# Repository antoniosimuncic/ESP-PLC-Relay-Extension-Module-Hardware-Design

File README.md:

# ESP-PLC-Relay-Extension-Module-Hardware-Design
ESP-PLC Relay-Extension-Module-Hardware-Design

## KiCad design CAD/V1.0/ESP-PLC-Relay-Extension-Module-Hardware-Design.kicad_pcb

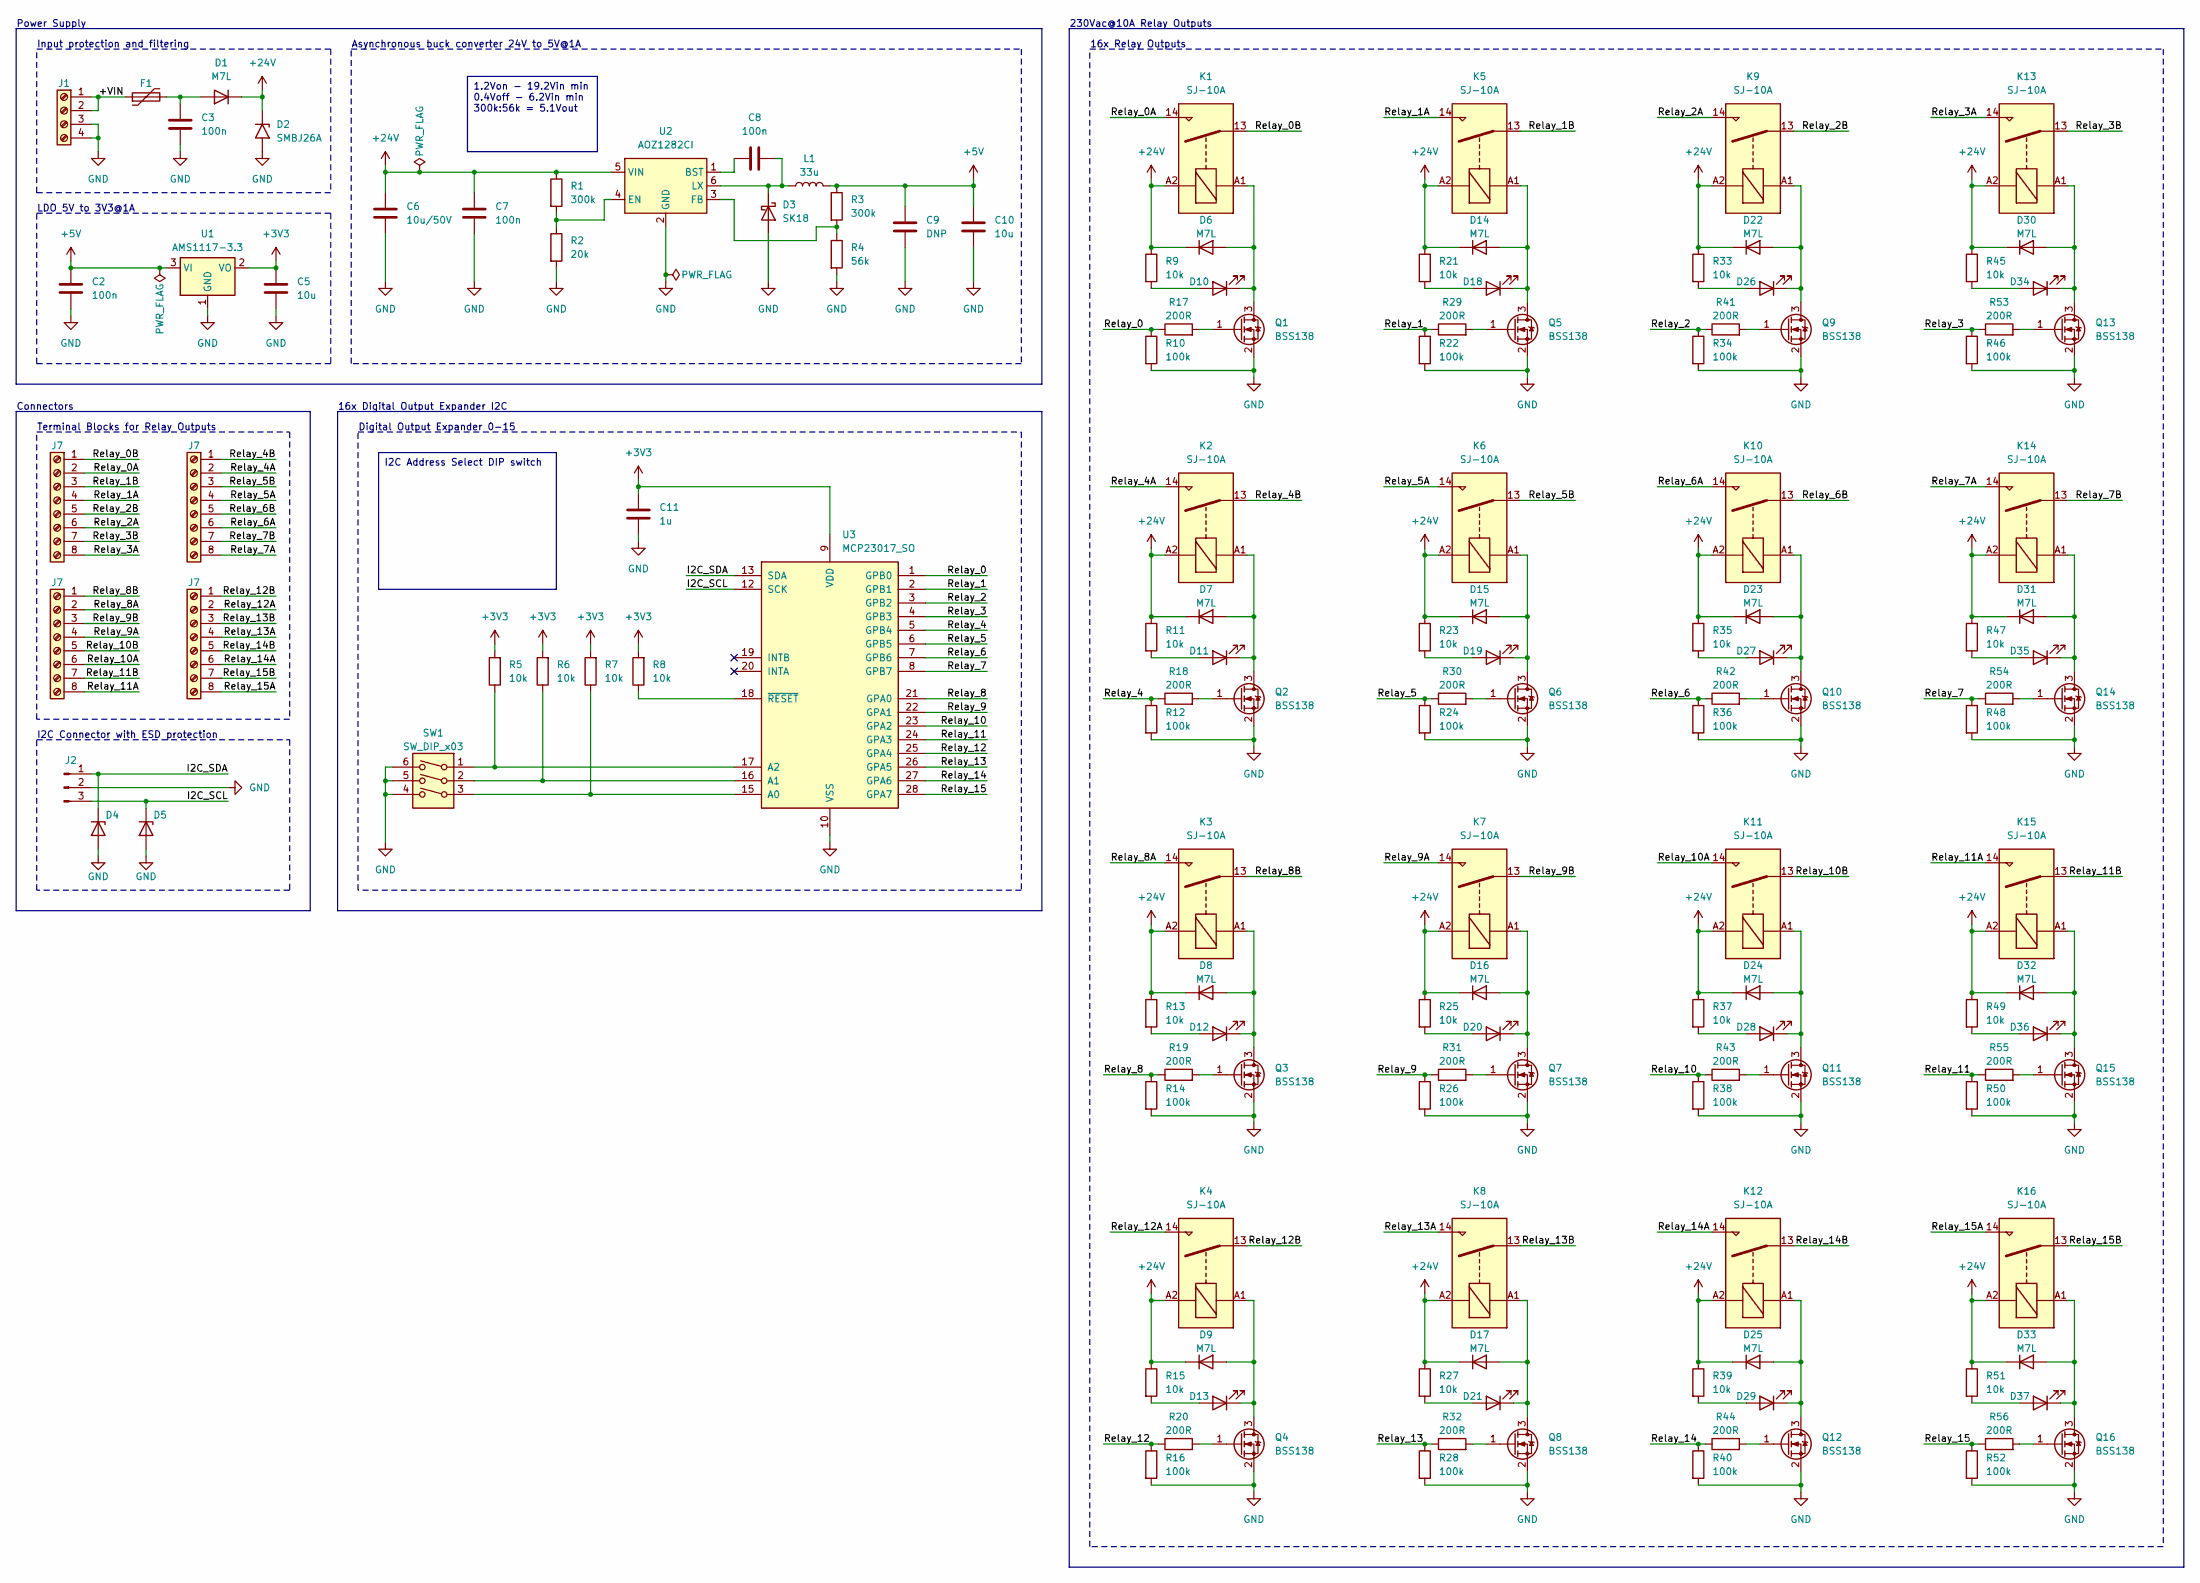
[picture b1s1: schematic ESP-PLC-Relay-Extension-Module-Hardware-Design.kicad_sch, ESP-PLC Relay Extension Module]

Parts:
C2, C3, C7, C8: 100n; C_0603_1608Metric
C5, C10: 10u; C_0805_2012Metric
C6: 10u/50V; C_1206_3216Metric
C9: DNP; C_0805_2012Metric
C11: 1u; C_0805_2012Metric
D1, D6, D7, D8, D9, D14, D15, D16, D17, D22, D23, D24, D25, D30, D31, D32, D33: M7L; D_SMA
D2: SMBJ26A; D_SMB
D3: SK18; D_SMA
D4, D5: ESD5Z3.3T1G; D_SOD-523
D10, D11, D12, D13, D18, D19, D20, D21, D26, D27, D28, D29, D34, D35, D36, D37: LED; LED_0805_2012Metric
F1: 0ZCH0010FF2E; Fuse_1210_3225Metric
J1: Screw_Terminal_01x04; PhoenixContact_MSTBVA_2,5_4-G-5,08_1x04_P5.08mm_Vertical
J2: Conn_01x03_Pin; JST_XH_B3B-XH-A_1x03_P2.50mm_Vertical
J7: Screw_Terminal_01x08; PhoenixContact_MSTBA_2,5_8-G-5,08_1x08_P5.08mm_Horizontal
K1, K2, K3, K4, K5, K6, K7, K8, K9, K10, K11, K12, K13, K14, K15, K16: SJ-10A; Relay_SJ-10A
L1: 33u; L_FerroCore_HPI1040_10.8x10.0mm
Q1, Q2, Q3, Q4, Q5, Q6, Q7, Q8, Q9, Q10, Q11, Q12, Q13, Q14, Q15, Q16: BSS138; SOT-23
R1, R3: 300k; R_0603_1608Metric
R2: 20k; R_0603_1608Metric
R4: 56k; R_0603_1608Metric
R5, R6, R7, R8, R9, R11, R13, R15, R21, R23, R25, R27, R33, R35, R37, R39, R45, R47, R49, R51: 10k; R_0603_1608Metric
R10, R12, R14, R16, R22, R24, R26, R28, R34, R36, R38, R40, R46, R48, R50, R52: 100k; R_0603_1608Metric
R17, R18, R19, R20, R29, R30, R31, R32, R41, R42, R43, R44, R53, R54, R55, R56: 200R; R_0603_1608Metric
SW1: SW_DIP_x03; SW_DIP_SPSTx03_Slide_9.78x9.8mm_W7.62mm_P2.54mm
U1: AMS1117-3.3; SOT-223-3_TabPin2
U2: AOZ1282CI; SOT-23-6
U3: MCP23017_SO; SOIC-28W_7.5x17.9mm_P1.27mm

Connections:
+3V3: C5.1, C11.1, R5.2, R6.2, R7.2, R8.2, U1.2 (VO), U3.9 (VDD)
+5V: C2.1, C9.1, C10.1, L1.2, R3.1, U1.3 (VI)
+24V: C6.1, C7.1, D1.1 (K), D2.1 (A1), D6.1 (K), D7.1 (K), D8.1 (K), D9.1 (K), D14.1 (K), D15.1 (K), D16.1 (K), D17.1 (K), D22.1 (K), D23.1 (K), D24.1 (K), D25.1 (K), D30.1 (K), D31.1 (K), D32.1 (K), D33.1 (K), K1.A2, K2.A2, K3.A2, K4.A2, K5.A2, K6.A2, K7.A2, K8.A2, K9.A2, K10.A2, K11.A2, K12.A2, K13.A2, K14.A2, K15.A2, K16.A2, R1.1, R9.1, R11.1, R13.1, R15.1, R21.1, R23.1, R25.1, R27.1, R33.1, R35.1, R37.1, R39.1, R45.1, R47.1, R49.1, R51.1, U2.5 (VIN)
/+VIN: F1.1, J1.1, J1.2
/I2C_SCL: D5.1 (K), J2.3, U3.12 (SCK)
/I2C_SDA: D4.1 (K), J2.1, U3.13 (SDA)
/Relay_0: R10.1, R17.1, U3.1 (GPB0)
/Relay_0A: K1.14; also elsewhere on the board
/Relay_0B: K1.13; also elsewhere on the board
/Relay_1: R22.1, R29.1, U3.2 (GPB1)
/Relay_1A: K5.14; also elsewhere on the board
/Relay_1B: K5.13; also elsewhere on the board
/Relay_2: R34.1, R41.1, U3.3 (GPB2)
/Relay_2A: K9.14; also elsewhere on the board
/Relay_2B: K9.13; also elsewhere on the board
/Relay_3: R46.1, R53.1, U3.4 (GPB3)
/Relay_3A: K13.14; also elsewhere on the board
/Relay_3B: K13.13; also elsewhere on the board
/Relay_4: R12.1, R18.1, U3.5 (GPB4)
/Relay_4A: K2.14; also elsewhere on the board
/Relay_4B: K2.13; also elsewhere on the board
/Relay_5: R24.1, R30.1, U3.6 (GPB5)
/Relay_5A: K6.14; also elsewhere on the board
/Relay_5B: K6.13; also elsewhere on the board
/Relay_6: R36.1, R42.1, U3.7 (GPB6)
/Relay_6A: K10.14; also elsewhere on the board
/Relay_6B: K10.13; also elsewhere on the board
/Relay_7: R48.1, R54.1, U3.8 (GPB7)
/Relay_7A: K14.14; also elsewhere on the board
/Relay_7B: K14.13; also elsewhere on the board
/Relay_8: R14.1, R19.1, U3.21 (GPA0)
/Relay_8A: K3.14; also elsewhere on the board
/Relay_8B: K3.13; also elsewhere on the board
/Relay_9: R26.1, R31.1, U3.22 (GPA1)
/Relay_9A: K7.14; also elsewhere on the board
/Relay_9B: K7.13; also elsewhere on the board
/Relay_10: R38.1, R43.1, U3.23 (GPA2)
/Relay_10A: K11.14; also elsewhere on the board
/Relay_10B: K11.13; also elsewhere on the board
/Relay_11: R50.1, R55.1, U3.24 (GPA3)
/Relay_11A: K15.14; also elsewhere on the board
/Relay_11B: K15.13; also elsewhere on the board
/Relay_12: R16.1, R20.1, U3.25 (GPA4)
/Relay_12A: K4.14; also elsewhere on the board
/Relay_12B: K4.13; also elsewhere on the board
/Relay_13: R28.1, R32.1, U3.26 (GPA5)
/Relay_13A: K8.14; also elsewhere on the board
/Relay_13B: K8.13; also elsewhere on the board
/Relay_14: R40.1, R44.1, U3.27 (GPA6)
/Relay_14A: K12.14; also elsewhere on the board
/Relay_14B: K12.13; also elsewhere on the board
/Relay_15: R52.1, R56.1, U3.28 (GPA7)
/Relay_15A: K16.14; also elsewhere on the board
/Relay_15B: K16.13; also elsewhere on the board
GND: C2.2, C3.2, C5.2, C6.2, C7.2, C9.2, C10.2, C11.2, D2.2 (A2), D3.2 (A), D4.2 (A), D5.2 (A), J1.3, J1.4, J2.2, Q1.2 (S), Q2.2 (S), Q3.2 (S), Q4.2 (S), Q5.2 (S), Q6.2 (S), Q7.2 (S), Q8.2 (S), Q9.2 (S), Q10.2 (S), Q11.2 (S), Q12.2 (S), Q13.2 (S), Q14.2 (S), Q15.2 (S), Q16.2 (S), R2.2, R4.2, R10.2, R12.2, R14.2, R16.2, R22.2, R24.2, R26.2, R28.2, R34.2, R36.2, R38.2, R40.2, R46.2, R48.2, R50.2, R52.2, SW1.4, SW1.5, SW1.6, U1.1 (GND), U2.2 (GND), U3.10 (VSS)
unnamed: C3.1, D1.2 (A), F1.2
unnamed: C8.1, D3.1 (K), L1.1, U2.6 (LX)
unnamed: D10.2 (A), R9.2
unnamed: D6.2 (A), D10.1 (K), K1.A1, Q1.3 (D)
unnamed: D11.2 (A), R11.2
unnamed: D7.2 (A), D11.1 (K), K2.A1, Q2.3 (D)
unnamed: D12.2 (A), R13.2
unnamed: D8.2 (A), D12.1 (K), K3.A1, Q3.3 (D)
unnamed: D13.2 (A), R15.2
unnamed: D9.2 (A), D13.1 (K), K4.A1, Q4.3 (D)
unnamed: D14.2 (A), D18.1 (K), K5.A1, Q5.3 (D)
unnamed: D15.2 (A), D19.1 (K), K6.A1, Q6.3 (D)
unnamed: D16.2 (A), D20.1 (K), K7.A1, Q7.3 (D)
unnamed: D17.2 (A), D21.1 (K), K8.A1, Q8.3 (D)
unnamed: D18.2 (A), R21.2
unnamed: D19.2 (A), R23.2
unnamed: D20.2 (A), R25.2
unnamed: D21.2 (A), R27.2
unnamed: D22.2 (A), D26.1 (K), K9.A1, Q9.3 (D)
unnamed: D23.2 (A), D27.1 (K), K10.A1, Q10.3 (D)
unnamed: D24.2 (A), D28.1 (K), K11.A1, Q11.3 (D)
unnamed: D25.2 (A), D29.1 (K), K12.A1, Q12.3 (D)
unnamed: D26.2 (A), R33.2
unnamed: D27.2 (A), R35.2
unnamed: D28.2 (A), R37.2
unnamed: D29.2 (A), R39.2
unnamed: D30.2 (A), D34.1 (K), K13.A1, Q13.3 (D)
unnamed: D31.2 (A), D35.1 (K), K14.A1, Q14.3 (D)
unnamed: D32.2 (A), D36.1 (K), K15.A1, Q15.3 (D)
unnamed: D33.2 (A), D37.1 (K), K16.A1, Q16.3 (D)
unnamed: D34.2 (A), R45.2
unnamed: D35.2 (A), R47.2
unnamed: D36.2 (A), R49.2
unnamed: D37.2 (A), R51.2
unnamed: Q1.1 (G), R17.2
unnamed: Q2.1 (G), R18.2
unnamed: Q3.1 (G), R19.2
unnamed: Q4.1 (G), R20.2
unnamed: Q5.1 (G), R29.2
unnamed: Q6.1 (G), R30.2
unnamed: Q7.1 (G), R31.2
unnamed: Q8.1 (G), R32.2
unnamed: Q9.1 (G), R41.2
unnamed: Q10.1 (G), R42.2
unnamed: Q11.1 (G), R43.2
unnamed: Q12.1 (G), R44.2
unnamed: Q13.1 (G), R53.2
unnamed: Q14.1 (G), R54.2
unnamed: Q15.1 (G), R55.2
unnamed: Q16.1 (G), R56.2
unnamed: C8.2, U2.1 (BST)
unnamed: R1.2, R2.1, U2.4 (EN)
unnamed: R3.2, R4.1, U2.3 (FB)
unnamed: R7.1, SW1.3, U3.15 (A0)
unnamed: R6.1, SW1.2, U3.16 (A1)
unnamed: R5.1, SW1.1, U3.17 (A2)
unnamed: R8.1, U3.18 (~RESET)

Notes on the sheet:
1.2Von - 19.2Vin min 0.4Voff - 6.2Vin min 300k:56k = 5.1Vout
I2C Address Select DIP switch
Terminal Blocks for Relay Outputs
Power Supply
16x Digital Output Expander I2C
230Vac@10A Relay Outputs
LDO 5V to 3V3@1A
Connectors
Digital Output Expander 0-15
16x Relay Outputs
Asynchronous buck converter 24V to 5V@1A
Input protection and filtering
I2C Connector with ESD protection

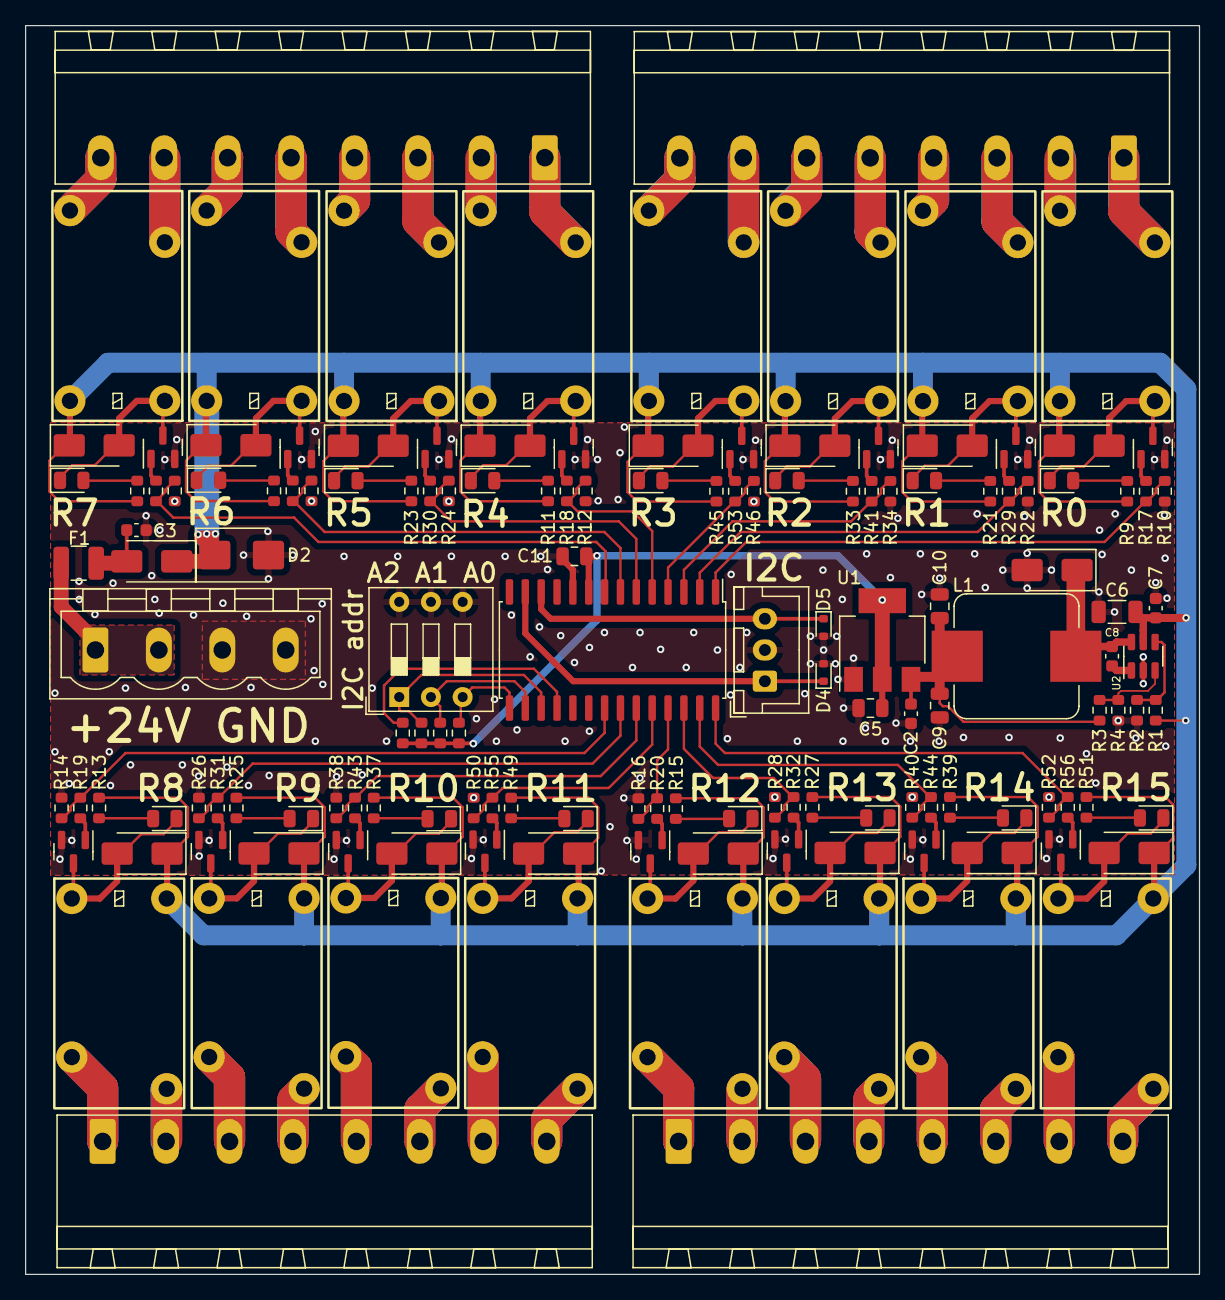
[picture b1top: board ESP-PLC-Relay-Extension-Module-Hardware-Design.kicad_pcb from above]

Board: 2 copper layers, 94.0 x 100.0 mm, 146 parts (0 on the bottom side), 112 nets.

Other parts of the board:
J3, J4, J5, J6: Screw_Terminal_01x08; PhoenixContact_MSTBA_2,5_8-G-5,08_1x08_P5.08mm_Horizontal

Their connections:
/Relay_0A: J3.2; also elsewhere on the board
/Relay_0B: J3.1; also elsewhere on the board
/Relay_1A: J3.4; also elsewhere on the board
/Relay_1B: J3.3; also elsewhere on the board
/Relay_2A: J3.6; also elsewhere on the board
/Relay_2B: J3.5; also elsewhere on the board
/Relay_3A: J3.8; also elsewhere on the board
/Relay_3B: J3.7; also elsewhere on the board
/Relay_4A: J5.2; also elsewhere on the board
/Relay_4B: J5.1; also elsewhere on the board
/Relay_5A: J5.4; also elsewhere on the board
/Relay_5B: J5.3; also elsewhere on the board
/Relay_6A: J5.6; also elsewhere on the board
/Relay_6B: J5.5; also elsewhere on the board
/Relay_7A: J5.8; also elsewhere on the board
/Relay_7B: J5.7; also elsewhere on the board
/Relay_8A: J4.2; also elsewhere on the board
/Relay_8B: J4.1; also elsewhere on the board
/Relay_9A: J4.4; also elsewhere on the board
/Relay_9B: J4.3; also elsewhere on the board
/Relay_10A: J4.6; also elsewhere on the board
/Relay_10B: J4.5; also elsewhere on the board
/Relay_11A: J4.8; also elsewhere on the board
/Relay_11B: J4.7; also elsewhere on the board
/Relay_12A: J6.2; also elsewhere on the board
/Relay_12B: J6.1; also elsewhere on the board
/Relay_13A: J6.4; also elsewhere on the board
/Relay_13B: J6.3; also elsewhere on the board
/Relay_14A: J6.6; also elsewhere on the board
/Relay_14B: J6.5; also elsewhere on the board
/Relay_15A: J6.8; also elsewhere on the board
/Relay_15B: J6.7; also elsewhere on the board

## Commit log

2024-02-09 remote commit
2024-02-09 Added Relays
2024-02-10 PCB designing
2024-02-11 PCB Routing
2024-02-12 Final Commit, files sent to JLCPCB
2024-02-12 added schematic and renamed bom
